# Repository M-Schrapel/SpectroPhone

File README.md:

#  :camera: SpectroPhone: Enabling Material Surface Sensing with RearCamera and Flashlight LEDs

This repository provides our code used for the paper: 
[`SpectroPhone: Enabling Material Surface Sensing with RearCamera and Flashlight LEDs`](https://dx.doi.org/10.1145/3411763.3451753)

Our contribution includes:
- **Dataset**
- **Application**

The repository is licensed under MIT licsense.

### Repository Structure

- Dataset: includes the recorded data
- Android App: Application for communicating with server, camera and additional hardware for controlling the LED
- Arduino: Software for the external RN2040 bluetooth connection
- Hardware: Eagle files for the board
- Phone case: case for the Huawei P20 smartphone
- Python Software: Server software for classifying images, training SVM models and viewing spectograms. Simply start main.py

## Dataset
Our dataset includes:
<details>
  <summary>30 different materials</summary>
  <p>prepared .csv files with calculated spectroscopic features</p>
</details>

## Citation
If you use our app and/or dataset in your projects, please use the following BibTeX citation:
```
@inproceedings{10.1145/3411763.3451753,
author = {Schrapel, Maximilian and Etgeton, Philipp and Rohs, Michael},
title = {SpectroPhone: Enabling Material Surface Sensing with RearCamera and Flashlight LEDs},
year = {2021},
isbn = {978-1-4503-8095-9/21/05},
publisher = {Association for Computing Machinery},
address = {New York, NY, USA},
url = {https://doi.org/10.1145/3411763.3451753 },
doi = {10.1145/3411763.3451753},
booktitle = {Extended Abstracts of the 2021 CHI Conference on Human Factors in Computing Systems},
articleno = {5},
numpages = {5},
keywords = {Material sensing, Pattern recognition, Mobile Interaction},
location = {Yokohama, Japan},
series = {CHI EA '21}
}
```

##

This repository is provided by the Human-Computer Interaction Group at the University Hannover, Germany. The code was mainly developed by Philipp Etgeton during his masters thesis. For additional details, see our [CHI'21 Extended Abstract](https://dx.doi.org/10.1145/3411763.3451753). 
The dataset and code is licsened under MIT license. For inquiries, please contact maximilian.schrapel@hci.uni-hannover.de
<br>:camera: :heavy_plus_sign: :iphone: :arrow_right: :bar_chart:

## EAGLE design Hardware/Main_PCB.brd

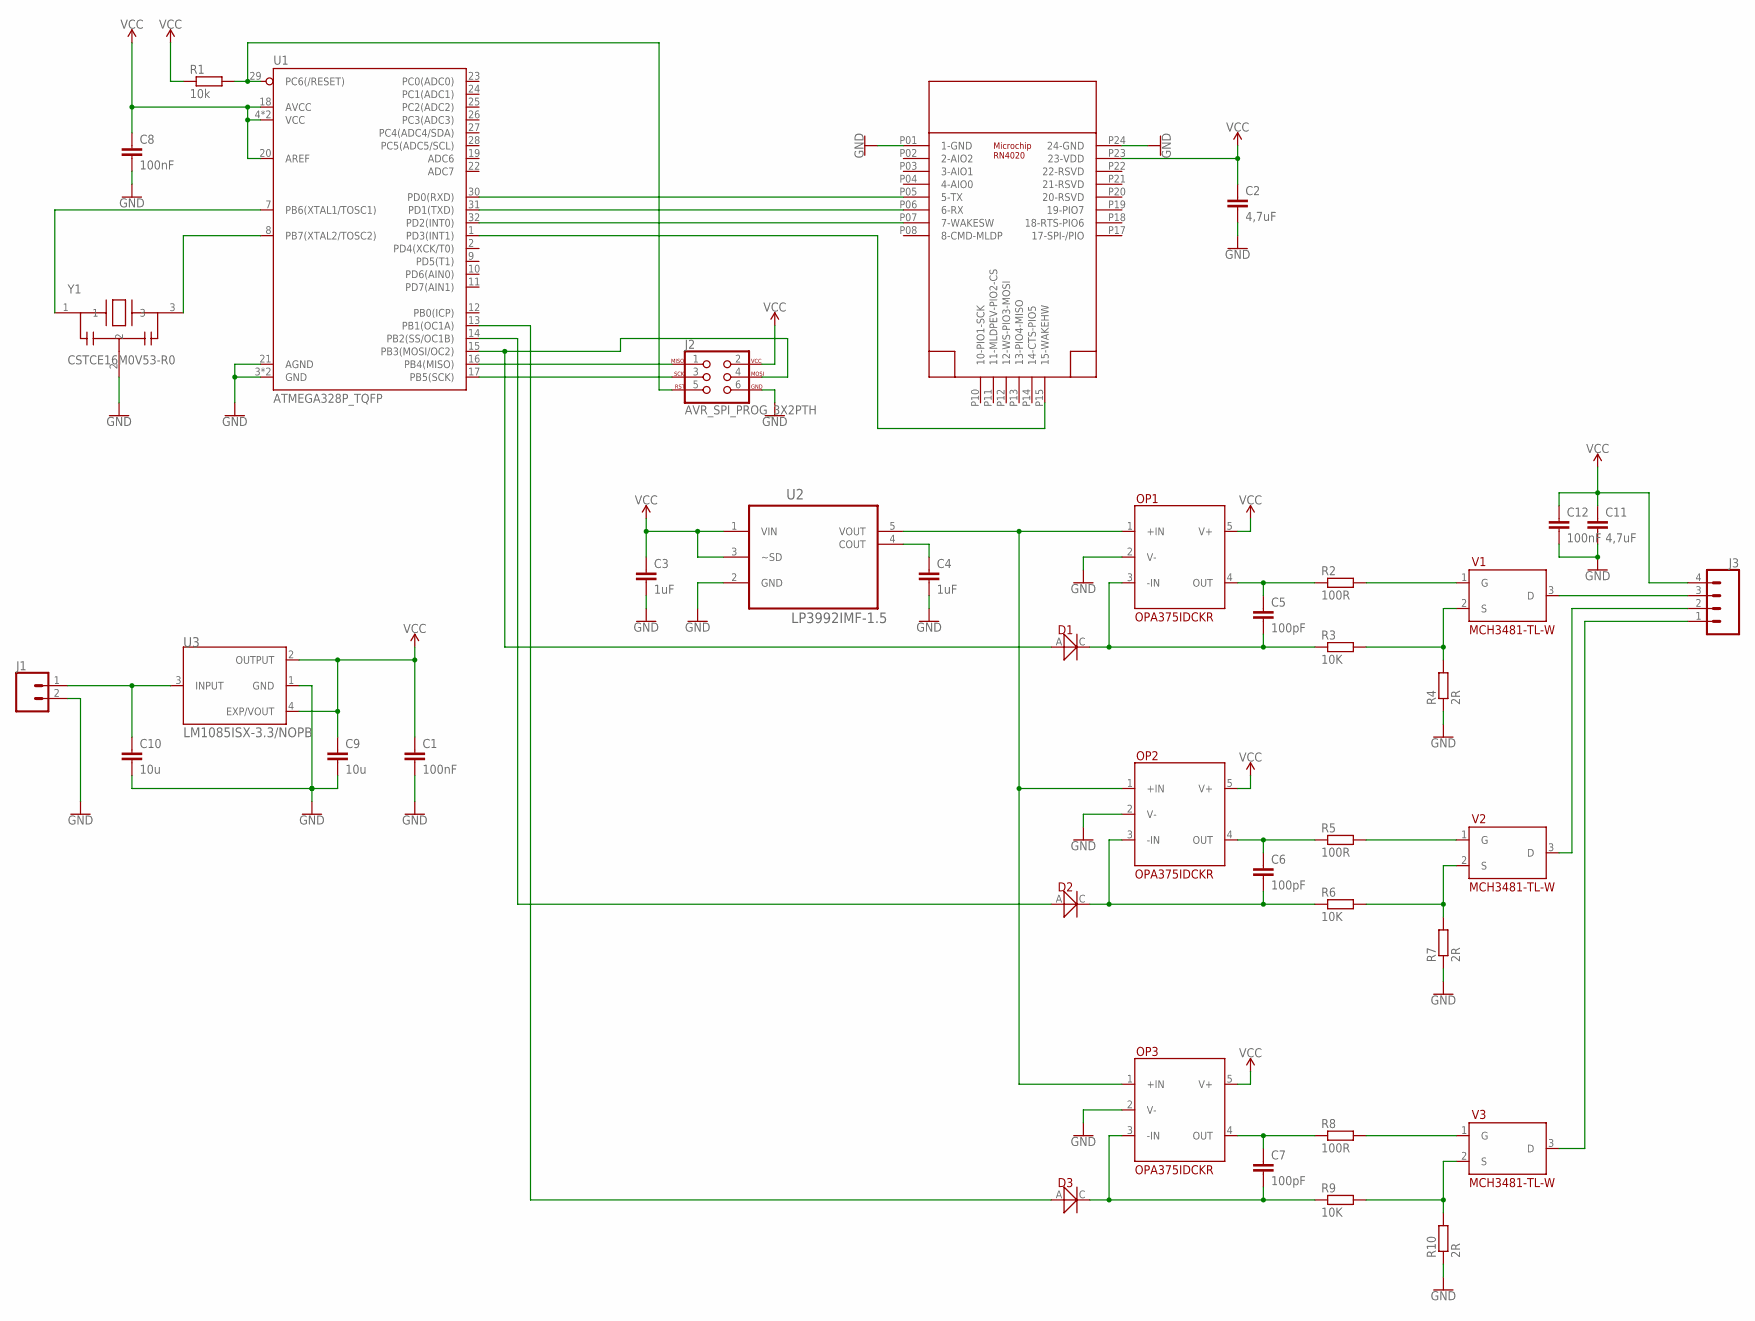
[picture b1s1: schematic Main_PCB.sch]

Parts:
C1, C8, C12: 100nF; C0805K
C2, C11: 4,7uF; C0805K
C3, C4: 1uF; C0805K
C5, C6, C7: 100pF; C0805K
C9, C10: 10u; C1206K
D1, D2, D3: 1N4148WQ-7-F; SOD-123
J1: CONN_02-JST-2MM-SMT; JST-2-SMD
J2: AVR_SPI_PROG_3X2PTH; 2X3
J3: CONN_04SMD; 1X04_SMD_RA_MALE
OP1, OP2, OP3: OPA375IDCKR; SC-70-05
R1: 10k; R0805
R2, R5, R8: 100R; R0805
R3, R6, R9: 10K; R0805
R4, R7, R10: 2R; R1210
U1: ATMEGA328P_TQFP; TQFP32-08
U2: LP3992IMF-1.5; SOT95P284X122-5N
U3: LM1085ISX-3.3/NOPB; DPAK254P1435X464-4N
U$1: RN4020; RN4020SMD
V1, V2, V3: MCH3481-TL-W; SC-70FL
Y1: CSTCE16M0V53-R0; OSC_CSTCE16M0V53-R0

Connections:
GND: C1.2, C2.2, C3.2, C4.2, C8.2, C9.2, C10.2, C11.2, C12.2, J1.2 (1), J2.6, OP1.2 (V-), OP2.2 (V-), OP3.2 (V-), R4.1, R7.1, R10.1, U1.3 (GND), U1.5 (GND), U1.21 (AGND), U2.2 (GND), U3.1 (GND), U$1.P01 (1-GND), U$1.P24 (24-GND), Y1.2
unnamed: J2.5, R1.2, U1.29 (PC6(/RESET))
unnamed: U1.30 (PD0(RXD)), U$1.P05 (5-TX)
unnamed: U1.31 (PD1(TXD)), U$1.P06 (6-RX)
unnamed: U1.32 (PD2(INT0)), U$1.P07 (7-WAKESW)
unnamed: U1.1 (PD3(INT1)), U$1.P15 (15-WAKEHW)
unnamed: C4.1, U2.4 (COUT)
unnamed: OP1.1 (+IN), OP2.1 (+IN), OP3.1 (+IN), U2.5 (VOUT)
unnamed: C5.1, OP1.4 (OUT), R2.1
unnamed: R3.2, R4.2, V1.2 (S)
unnamed: J2.1, U1.16 (PB4(MISO))
unnamed: R2.2, V1.1 (G)
unnamed: C5.2, D1.C (CATHODE), OP1.3 (-IN), R3.1
unnamed: J3.3, V1.3 (D)
unnamed: C6.2, D2.C (CATHODE), OP2.3 (-IN), R6.1
unnamed: C6.1, OP2.4 (OUT), R5.1
unnamed: R6.2, R7.2, V2.2 (S)
unnamed: U1.8 (PB7(XTAL2/TOSC2)), Y1.3
unnamed: R5.2, V2.1 (G)
unnamed: J3.2, V2.3 (D)
unnamed: C7.2, D3.C (CATHODE), OP3.3 (-IN), R9.1
unnamed: C7.1, OP3.4 (OUT), R8.1
unnamed: R9.2, R10.2, V3.2 (S)
unnamed: U1.7 (PB6(XTAL1/TOSC1)), Y1.1
unnamed: R8.2, V3.1 (G)
unnamed: J3.1, V3.3 (D)
unnamed: D1.A (ANODE), J2.4, U1.15 (PB3(MOSI/OC2))
unnamed: D2.A (ANODE), U1.14 (PB2(SS/OC1B))
unnamed: D3.A (ANODE), U1.13 (PB1(OC1A))
unnamed: J2.3, U1.17 (PB5(SCK))
unnamed: C10.1, J1.1 (2), U3.3 (INPUT)
VCC: C1.1, C2.1, C3.1, C8.1, C9.1, C11.1, C12.1, J2.2, J3.4, OP1.5 (V+), OP2.5 (V+), OP3.5 (V+), R1.1, U1.4 (VCC), U1.6 (VCC), U1.18 (AVCC), U1.20 (AREF), U2.1 (VIN), U2.3 (~SD), U3.2 (OUTPUT), U3.4 (EXP/VOUT), U$1.P23 (23-VDD)

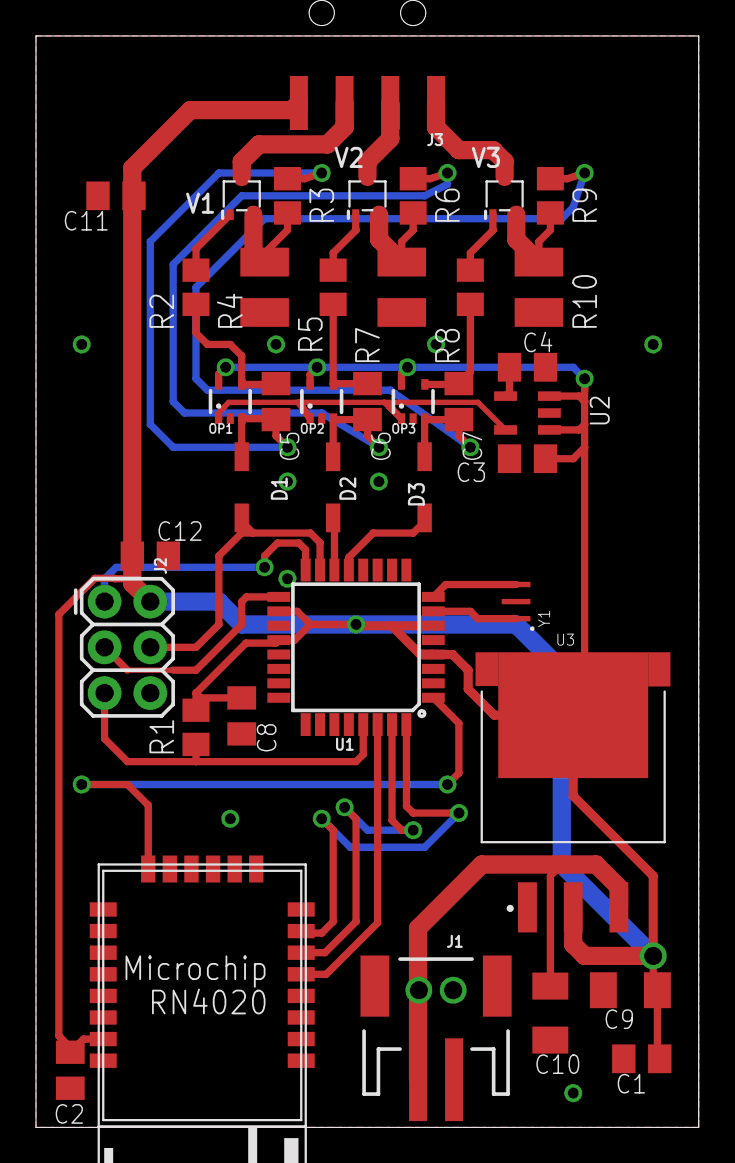
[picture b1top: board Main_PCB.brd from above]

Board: 2 copper layers, 36.8 x 60.6 mm, 39 parts (0 on the bottom side), 32 nets.

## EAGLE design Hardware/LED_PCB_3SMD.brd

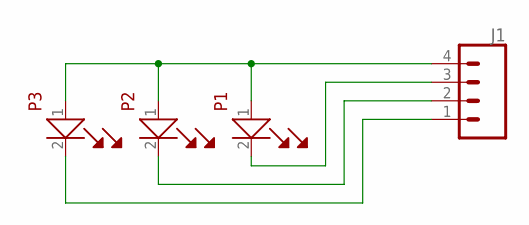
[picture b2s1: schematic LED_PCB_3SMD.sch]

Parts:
J1: CONN_04LONGPADS; 1X04_LONGPADS
P1, P2, P3: OSRAM-LED; SMD-2

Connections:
unnamed: J1.4, P1.1 (ANODE), P2.1 (ANODE), P3.1 (ANODE)
unnamed: J1.3, P1.2 (CATHODE)
unnamed: J1.2, P2.2 (CATHODE)
unnamed: J1.1, P3.2 (CATHODE)

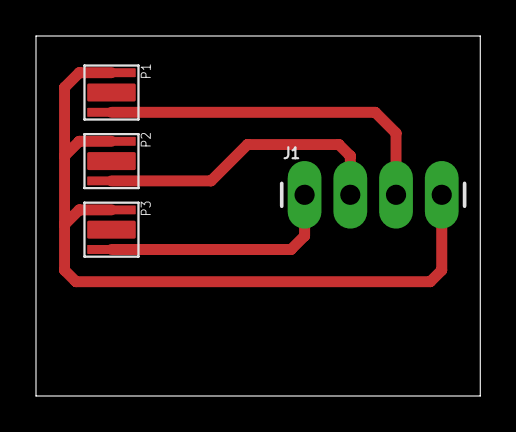
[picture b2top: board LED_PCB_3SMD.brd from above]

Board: 2 copper layers, 24.7 x 20.0 mm, 4 parts (0 on the bottom side), 4 nets.

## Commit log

2021-05-07 added institute image

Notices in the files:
parts and their libraries:
SparkFun-Connectors: Licensing: Creative Commons ShareAlike 4.0 International - https://creativecommons.org/licenses/by-sa/4.0
